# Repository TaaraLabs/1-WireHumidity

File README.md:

1-WireHumidity
==============

1-Wire Humidity and Temperature sensor

[WebSite](https://taaralabs.eu/oh1)

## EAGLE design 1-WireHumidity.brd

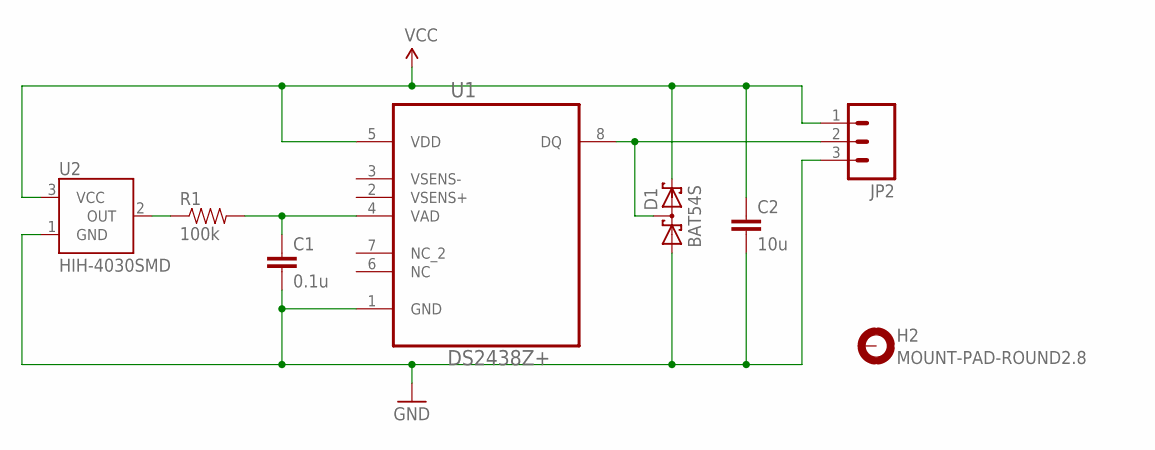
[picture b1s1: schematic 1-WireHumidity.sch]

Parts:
C1: 0.1u; 0603-CAP
C2: 10u; 0603-CAP
D1: BAT54S; SOT23
H2: MOUNT-PAD-ROUND2.8; 2,8-PAD
JP2: M03LONGPADS; 1X03_LONGPADS
R1: 100k; 0603-RES
U1: DS2438Z+; SOIC127P600X175-8N
U2: HIH-4030SMD; HIH-4030

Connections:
GND: C1.2, C2.2, D1.1 (A1), JP2.3, U1.1 (GND), U2.1 (GND)
unnamed: R1.1, U2.2 (OUT)
QD: D1.3 (C1A2), JP2.2, U1.8 (DQ)
VAD: C1.1, R1.2, U1.4 (VAD)
VCC: C2.1, D1.2 (C2), JP2.1, U1.5 (VDD), U2.3 (VCC)

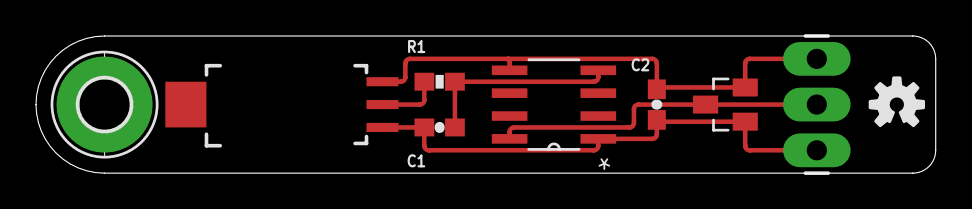
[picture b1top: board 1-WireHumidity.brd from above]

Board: 2 copper layers, 50.0 x 7.6 mm, 10 parts (1 on the bottom side), 5 nets.

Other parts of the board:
U$1, U$3: OSHW-LOGO-S

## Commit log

2014-12-29 :boom::camel: Added .gitattributes & .gitignore files
2014-12-29 1-Wire Humidity and Temperature sensor
    Sensor based on DS2438 1-Wire ADC with integrated temperature sensor and
    HIH-4030 analog humidity sensor
2014-12-29 Pictures of schematic and board layout
2014-12-29 Added link to the website
2015-02-17 Little board lenght adjustment (now 5cm)
2015-02-17 Added picture of the assembled sensor
2015-02-17 Added picture of the full kit of the sensor assembly
2015-02-17 Added picture of the PCB

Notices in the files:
parts and their libraries:
SparkFun-Sensors: Licensing: CC v3.0 Share-Alike You are welcome to use this library for commercial purposes.
